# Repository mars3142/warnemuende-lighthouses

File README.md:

| Supported Targets | ESP32 | ESP32-C3 | ESP32-C5 | ESP32-C6 | ESP32-H2 | ESP32-P4 | ESP32-S3 |
| ----------------- | ----- | -------- | -------- | -------- | -------- | -------- | -------- |

# Mole Beacon

You can find more about it on [my wiki](https://wiki.mars3142.dev/project/maerklin/warnemuende/lighthouse/start).

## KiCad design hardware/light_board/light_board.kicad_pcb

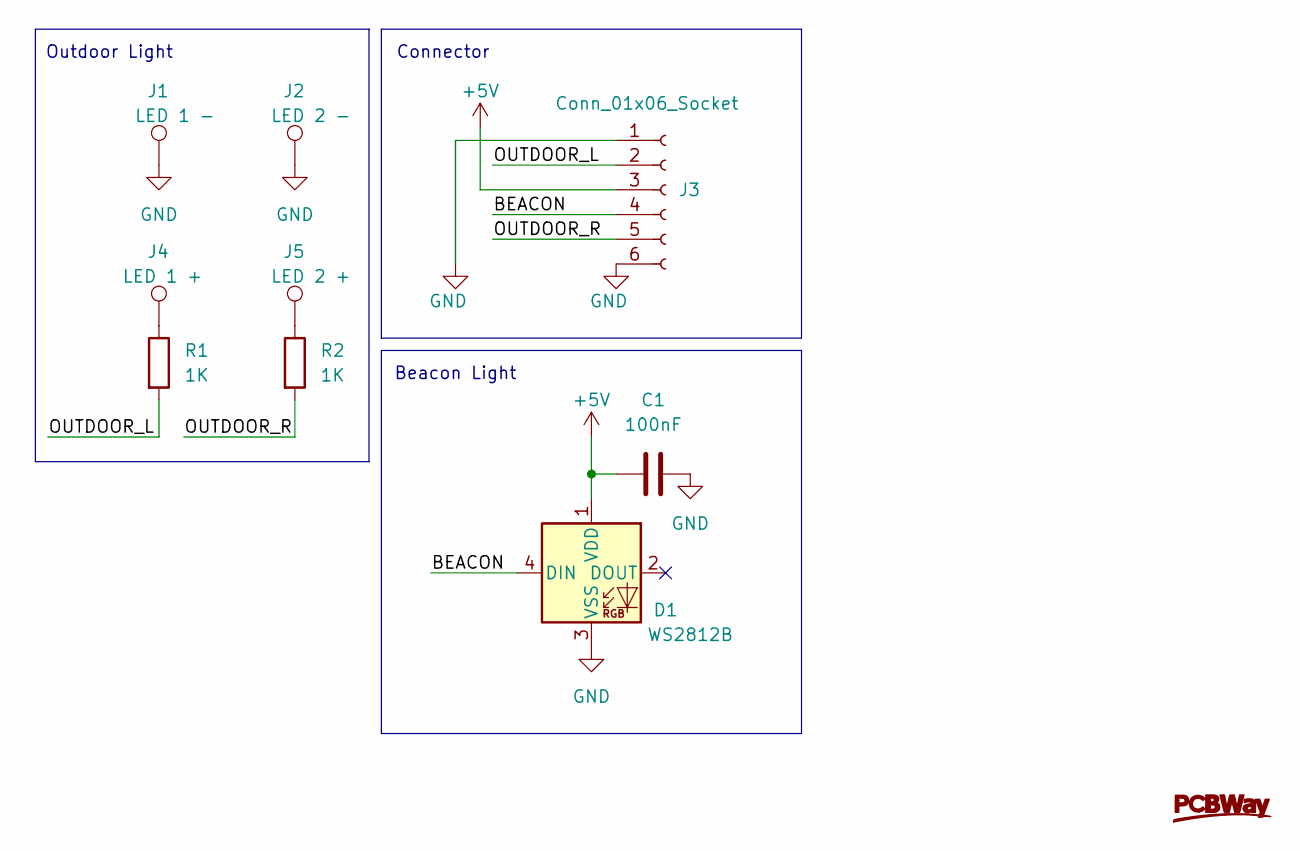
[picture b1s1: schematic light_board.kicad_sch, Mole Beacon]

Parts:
C1: 100nF; C_0805_2012Metric_Pad1.18x1.45mm_HandSolder
D1: WS2812B; LED_WS2812B_PLCC4_5.0x5.0mm_P3.2mm; MPN 1212; LCSC 511-STM32F405RGT6
J1: LED 1 -; SolderWire-0.1sqmm_1x01_D0.4mm_OD1mm
J2: LED 2 -; SolderWire-0.1sqmm_1x01_D0.4mm_OD1mm
J3: Conn_01x06_Socket; JST_PH_B6B-PH-K_1x06_P2.00mm_Vertical
J4: LED 1 +; SolderWire-0.1sqmm_1x01_D0.4mm_OD1mm
J5: LED 2 +; SolderWire-0.1sqmm_1x01_D0.4mm_OD1mm
R1, R2: 1K; R_0805_2012Metric_Pad1.20x1.40mm_HandSolder

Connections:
+5V: C1.1, D1.1 (VDD), J3.3
/BEACON: D1.4 (DIN), J3.4
/OUTDOOR_L: J3.2, R1.2
/OUTDOOR_R: J3.5, R2.2
GND: C1.2, D1.3 (VSS), J1.1, J2.1, J3.1, J3.6
unnamed: J4.1, R1.1
unnamed: J5.1, R2.1

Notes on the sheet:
Beacon Light
Outdoor Light
Connector

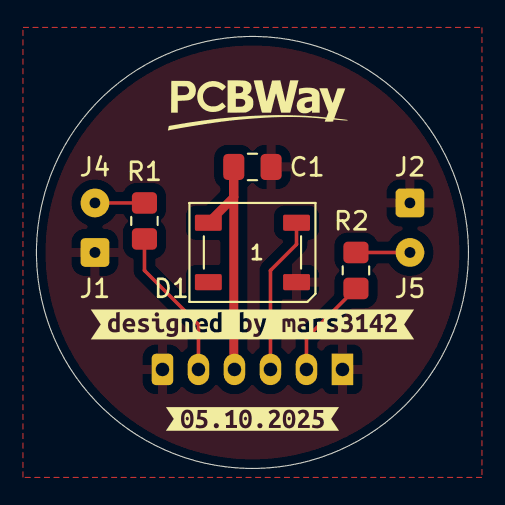
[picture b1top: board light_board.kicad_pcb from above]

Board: 2 copper layers, 24.0 x 24.0 mm, 11 parts (1 on the bottom side), 7 nets.

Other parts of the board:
kibuzzard-6876A324: G***; kibuzzard-6876A324
kibuzzard-68711898: G***; kibuzzard-68711898

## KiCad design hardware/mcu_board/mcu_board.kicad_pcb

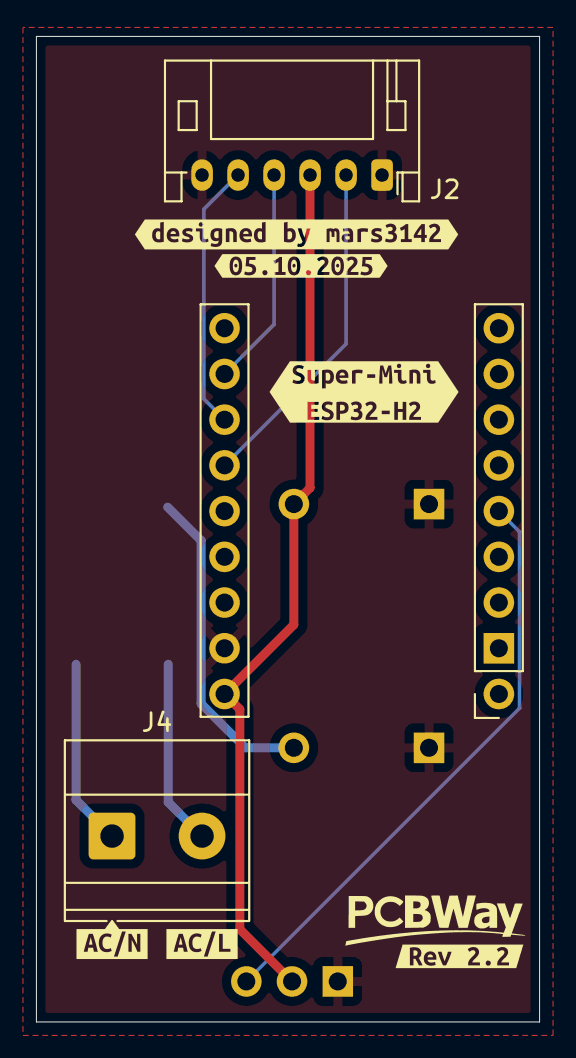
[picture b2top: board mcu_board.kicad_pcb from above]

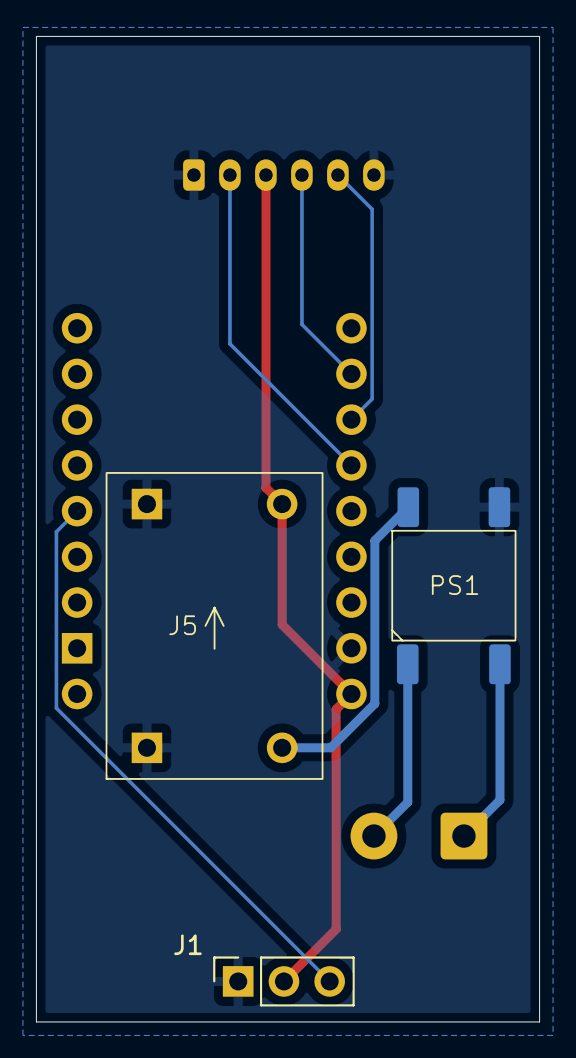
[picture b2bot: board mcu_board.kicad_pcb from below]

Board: 2 copper layers, 28.0 x 54.8 mm, 12 parts (3 on the bottom side), 9 nets.

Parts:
J1: Touch; PinSocket_1x03_P2.54mm_Vertical
J2: Light; JST_PH_S6B-PH-K_1x06_P2.00mm_Horizontal
J3: Conn_ESP32-H2_Super-Mini_-_Pins_only; PinSocket_H2 Super-Mini
J4: Input; TerminalBlock_Phoenix_MKDS-1,5-2_1x02_P5.00mm_Horizontal
J5: Buck Converter (30V to 5V)
PS1: DB407S
kibuzzard-68F9205C: G***; kibuzzard-68F9205C
kibuzzard-68F9220B: G***; kibuzzard-68F9220B
kibuzzard-68F92064: G***; kibuzzard-68F92064
kibuzzard-689F9361: G***; kibuzzard-689F9361
kibuzzard-6876C4C3: G***; kibuzzard-6876C4C3
kibuzzard-6876C573: G***; kibuzzard-6876C573

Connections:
+5V: J1.2, J2.3, J3.10 (5V), J5.4 (OUT+)
/AC/L: J4.2, PS1.1 (AC/L)
/AC/N: J4.1, PS1.2 (AC/N)
/BEACON: J2.4, J3.17 (GP10)
/IO: J1.3, J3.5 (GP2)
/OUTDOOR_L: J2.2, J3.15 (GP12)
/OUTDOOR_R: J2.5, J3.16 (GP11)
GND: J1.1, J2.1, J2.6, J3.11 (GND), J5.1 (IN-), J5.3 (OUT-), PS1.3 (-Vout)
VCC: J5.2 (IN+), PS1.4 (+Vout)

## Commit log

2025-06-06 empty project
2025-06-06 code splitting
2025-06-06 save artifacts
2025-06-07 led is blinking
2025-06-07 split matrix to simulate outdoor light
2025-06-07 replace queue with semaphore
2025-06-07 add license
2025-06-07 copy BLE functions
2025-06-07 add CODE_OF_CONDUCT.md
2025-06-07 Update issue templates
2025-06-07 new LED matrix pattern
2025-06-07 update github action trigger
2025-06-07 reorganize code
    create light service, with splitted beacon and outdoor functions
2025-06-13 updated github action
2025-06-13 change persistence namespace
2025-06-13 update github actions
2025-06-13 Revert "change persistence namespace"
    This reverts commit ef8f6e597e279cafcb5182b5d223cb12ef041ed2.
2025-06-13 code optimize
2025-07-26 updated esp-idf version in github action
2025-08-16 switch to ESP32-H2
2025-08-20 move firmware into subfolder
2025-08-23 folder cleanup
2025-08-26 update BLE advertisment
2025-08-27 more characteristics and descriptors
2025-08-27 fixing build
2025-08-28 simulation of a defective light bulb
2025-08-28 mv .github .gitea
    now the action will only run on gitea
2025-08-28 testing new action
2025-08-28 mv .gitea .github
    also add merge_bin
2025-08-29 try to implement uart over ble
    write is working (print into log), but notify doesn't work yet
2025-08-29 code clean up and persistence for beacon last state
2025-08-31 add custom PCBs
2025-09-01 testing touch interface for physical switching
2025-09-03 add symbol library
2025-09-04 latest mcu_board revision
    added buck converter
2025-09-11 add sponsor to PCBs
2025-09-16 latest custom library
2025-09-16 new mcu board design
2025-09-16 move actions to gitea
2025-09-16 remove issue templates
2025-09-16 add fail-fast
2025-09-16 more idf versions
2025-09-20 some tweeks for hardware
2025-09-20 add BLE bonding
2026-04-24 add matter
2026-04-24 latest KiCad changes
2026-05-31 implement openthread
2026-05-31 README.md aktualisiert
2026-05-31 .gitea/workflows/esp32_build.yaml aktualisiert
2026-05-31 updated external library
